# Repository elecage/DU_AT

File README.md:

# 열린플랫폼을 활용한 지역기반 보조기기 R&SD
환영합니다. 이 페이지는 동서울대학교, 인하대학교, 성남시장애인종합복지관이 공동으로 운영하는 지역기반 보조기기 R&amp;SD 과제의 보조기기 관리를 위해 만들어졌습니다.

## 과제 개요
  * 주관연구기관 : 동서울대학교산학협력단
  * 공동연구기관 : 인하대학교산학협력단/성남시장애인종합복지관
  * 연구기간 : 2024.04.01 - 2027.12.31
  * 주관 부처 : 보건복지부 국립재활원

## 과제 목표

## 보조기기 개발 프로세스

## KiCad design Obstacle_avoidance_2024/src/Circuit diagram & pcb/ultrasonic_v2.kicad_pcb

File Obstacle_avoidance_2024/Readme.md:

# 장애물 탐지 바닥센서

* 본 보조기기는 휠체어에 부착하여 후방의 장애물을 탐지하는 보조기기이다.
* 전동휠체어와 일반 휠체어에 부착하여 후진시 역과사고를 방지하는 것을 목적으로 한다.

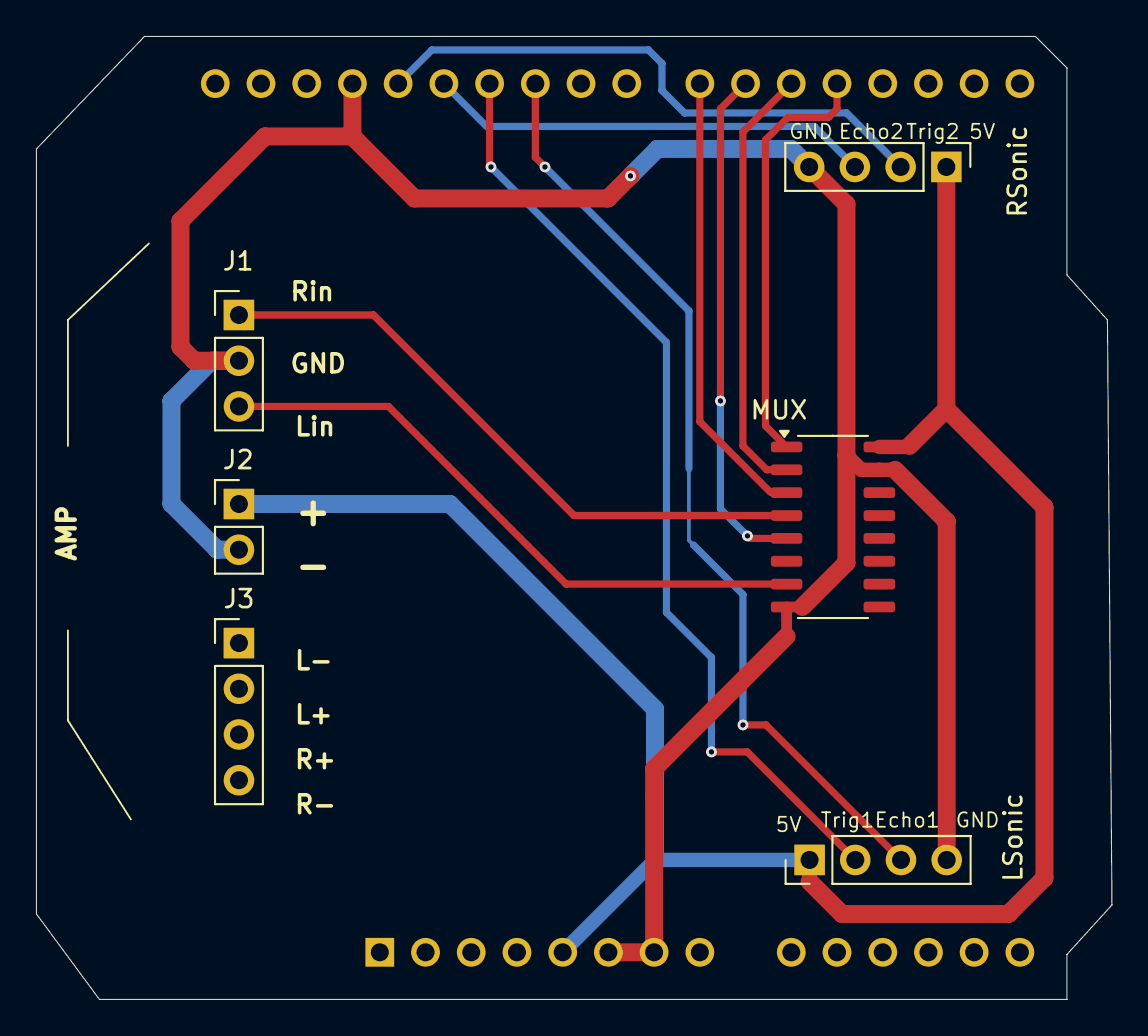
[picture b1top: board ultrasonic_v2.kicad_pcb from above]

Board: 2 copper layers, 59.8 x 53.5 mm, 7 parts (1 on the bottom side), 12 nets.

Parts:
A1: Arduino_UNO_R3
J1: Conn_01x03; PinHeader_1x03_P2.54mm_Vertical
J2: Conn_01x02; PinHeader_1x02_P2.54mm_Vertical
J3: Conn_01x04; PinHeader_1x04_P2.54mm_Vertical
LSonic: Conn_01x04; PinHeader_1x04_P2.54mm_Vertical
MUX: 74LS157; SO-16_3.9x9.9mm_P1.27mm
RSonic: Conn_01x04; PinHeader_1x04_P2.54mm_Vertical

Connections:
+5V: A1.5 (+5V), J2.1, LSonic.1, MUX.16 (VCC), RSonic.1
/Echo1_pin: A1.25 (D10), RSonic.3
/Echo2_pin: A1.27 (D12), LSonic.3
/SND_IN_L: J1.3, MUX.7 (Zb)
/SND_IN_R: J1.1, MUX.4 (Za)
/Trig1_pin: A1.26 (D11), RSonic.2
/Trig2_pin: A1.28 (D13), LSonic.2
GND: A1.6 (GND), A1.7 (GND), A1.29 (GND), J1.2, J2.2, LSonic.4, MUX.8 (GND), MUX.15 (E), RSonic.4
unnamed: A1.19 (D4), MUX.1 (S)
unnamed: A1.20 (D5), MUX.2 (I0a)
unnamed: A1.21 (D6), MUX.5 (I0b)
unnamed: A1.22 (D7), MUX.3 (I1a), MUX.6 (I1b)

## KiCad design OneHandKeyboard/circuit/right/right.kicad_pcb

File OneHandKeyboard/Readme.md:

# 한손키보드
## 

## Bill of Materials

| 품목 | 품명 | 규격 | 수량 | 구매처 |
|---|---|---|---|---|
|아크릴판| . | 1.5T | 1 | 문구점 |
|터치패드 모듈 |  TM035035-2024-001 | 커패시턴스 터치 센서 모듈 35mm Round SPI/I2C adhesive overlay | 1 | https://www.devicemart.co.kr/goods/view?no=15469948 |
| 볼트 | . | M2x4mm | 10 | . |
| 스탠드오프 | . | M2x8mm x 5mm(두께) | 5 | http://e.tb.cn/h.TWjAYGBWXisILQ2?tk=BHXE3v5Qo8o |
| PCB | 자체제작 | 왼손/오른손| 1| . |
|하우징 | 자체제작 | PLA | 1 | . |
|와이어 | . |. |. |.|
|마그네틱 포고핀| . | 수컷 암컷 간격, 2.5mm 용수철 부하| 1set|https://a.aliexpress.com/_oBtp4LP|
| 저소음스위치|.|Cherry MX 호환, 저소음 | 29 | .|
|키캡 | . |Cherry MX 호환, 무각 |. |.|
|펌웨어 | 자체제작 | . | . | .|

## 키보드 연습 사이트
https://cosmosalad.github.io/onekeytype/

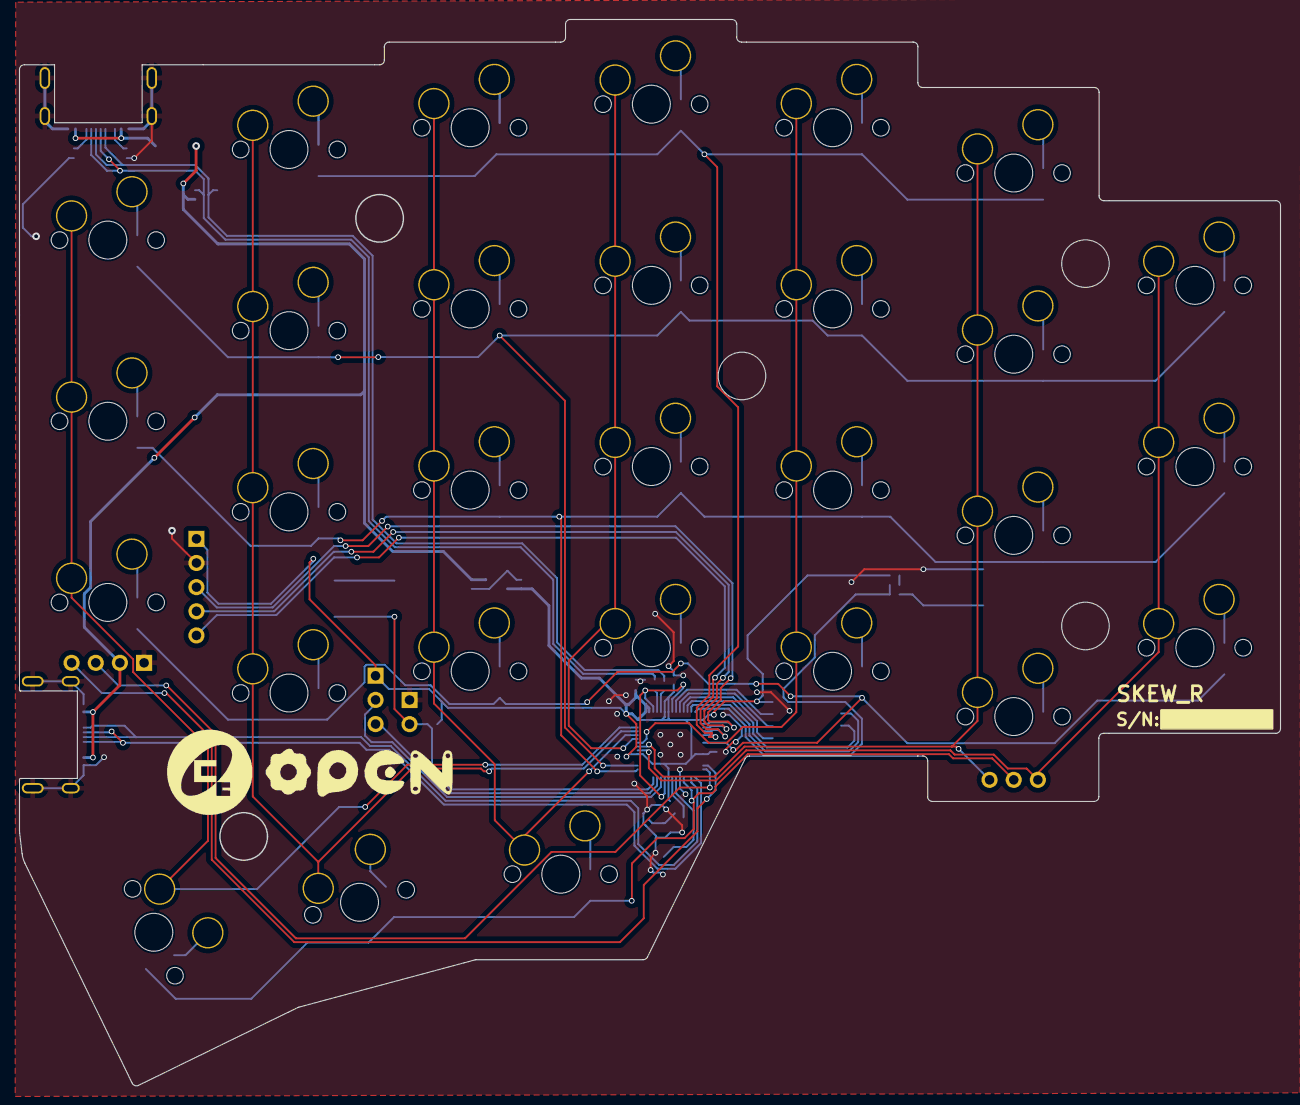
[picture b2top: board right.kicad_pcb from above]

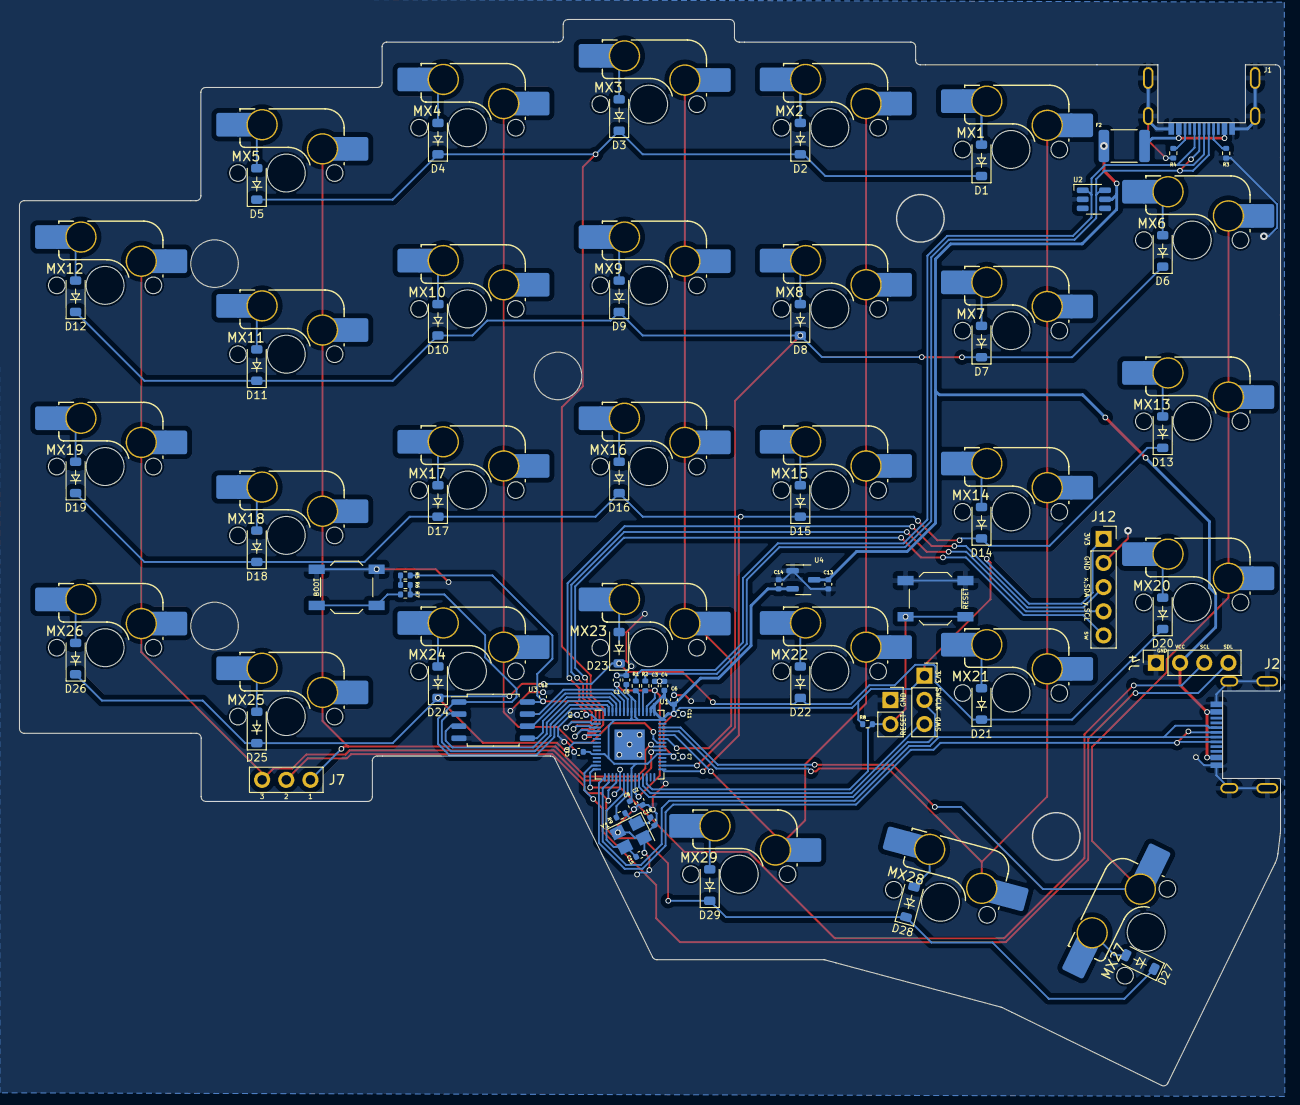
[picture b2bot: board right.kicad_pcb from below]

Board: 2 copper layers, 132.5 x 112.1 mm, 98 parts (96 on the bottom side), 73 nets.

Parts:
BOOT2: SW_Push; SW_SPST_TL3342
C1, C2, C4, C5, C6, C7, C8, C9, C10: 100n; C_0402_1005Metric
C3, C11, C12, C13, C14: 1u; C_0402_1005Metric
C15, C16: 22p; C_0402_1005Metric
D1, D2, D3, D4, D5, D6, D7, D8, D9, D10, D11, D12, D13, D14, D15, D16, D17, D18, D19, D20, D21, D22, D23, D24, D25, D26, D27, D28, D29: D_Small; D_SOD-123_new
F2: MF-MSMF050-2; Fuse_1812_4532Metric
J1, J2: TYPE-C-31-M-13; HRO-TYPE-C-31-M-13
J3: SWD_PinSocket; PinSocket_1x03_P2.54mm_Vertical
J4: PinSocket_4P; PinHeader_1x04_P2.54mm_Vertical
J6: PinSocket_5P; PinHeader_1x05_P2.54mm_Vertical
J7: side_b_PinSocket; PinSocket_1x03_P2.54mm_Vertical
MX1, MX2, MX3, MX4, MX5, MX6, MX7, MX8, MX9, MX10, MX11, MX12, MX13, MX14, MX15, MX16, MX17, MX18, MX19, MX20, MX21, MX22, MX23, MX24, MX25, MX26, MX28, MX29: kailh hotswap socket; SW_MX_HS_1u
MX27: kailh hotswap socket; SW_MX_HS_1.5u
R1, R2: 27; R_0402_1005Metric
R3, R4, R5, R6, R8: 5.1k; R_0402_1005Metric
R7, R9: 1k; R_0402_1005Metric
RESET1: SW_Push; SW_SPST_TL3342
RESET2: PinSocket_2P; PinSocket_1x02_P2.54mm_Vertical
U1: RP2040; QFN-56-1EP_7x7mm_P0.4mm_EP3.2x3.2mm
U2: SRV05-4; SOT-23-6-routable
U3: W25Q128JVSIQ; SOIC-8_5.23x5.23mm_P1.27mm
U4: XC6206P332MR; SOT-23-3
Y1: X322512MSB4SI; Crystal_SMD_3225-4Pin_3.2x2.5mm

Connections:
+1V1R: C1.1, C2.1, C3.1, U1.23 (DVDD), U1.45 (VREG_VOUT), U1.50 (DVDD)
+3V3R: C4.1, C5.1, C6.1, C7.1, C8.1, C9.1, C10.1, C11.1, C12.1, C14.1, J3.1, J6.1, R5.2, R8.2, U1.1 (IOVDD), U1.10 (IOVDD), U1.22 (IOVDD), U1.33 (IOVDD), U1.42 (IOVDD), U1.43 (ADC_AVDD), U1.44 (VREG_IN), U1.48 (USB_VDD), U1.49 (IOVDD), U3.8 (VCC), U4.2 (VO)
+5VR: C13.1, F2.1, J2.A4 (VBUS), J2.A9 (VBUS), J2.B4 (VBUS), J2.B9 (VBUS), J4.2, U2.5 (VP), U4.3 (VI)
COL0_R: J7.3, MX12.1, MX19.1, MX26.1, U1.34 (GPIO22)
COL1_R: J7.1, MX5.1, MX11.1, MX18.1, MX25.1, U1.35 (GPIO23)
COL2_R: MX4.1, MX10.1, MX17.1, MX24.1, U1.36 (GPIO24)
COL3_R: MX3.1, MX9.1, MX16.1, MX23.1, U1.37 (GPIO25)
COL4_R: MX2.1, MX8.1, MX15.1, MX22.1, MX29.1, U1.38 (GPIO26_ADC0)
COL5_R: MX1.1, MX7.1, MX14.1, MX21.1, MX28.1, U1.39 (GPIO27_ADC1)
COL6_R: MX6.1, MX13.1, MX20.1, MX27.1, U1.40 (GPIO28_ADC2)
GNDR: BOOT2.1, C1.2, C2.2, C3.2, C4.2, C5.2, C6.2, C7.2, C8.2, C9.2, C10.2, C11.2, C12.2, C13.2, C14.2, C15.2, C16.1, J1.A1 (GND), J1.A12 (GND), J1.B1 (GND), J1.B12 (GND), J1.S1 (SHIELD), J2.A1 (GND), J2.A12 (GND), J2.B1 (GND), J2.B12 (GND), J2.S1 (SHIELD), J4.1, J6.2, R3.2, R4.2, RESET1.1, RESET2.1, U1.19 (TESTEN), U1.57 (GND), U2.2 (VN), U3.4 (GND), U4.1 (GND), Y1.2, Y1.4
unnamed: BOOT2.2, R7.1
unnamed: C16.2, R9.1, Y1.1
unnamed: D1.2 (A), MX1.2
unnamed: D2.2 (A), MX2.2
unnamed: D3.2 (A), MX3.2
unnamed: D4.2 (A), MX4.2
unnamed: D5.2 (A), MX5.2
unnamed: D6.2 (A), MX6.2
unnamed: D7.2 (A), MX7.2
unnamed: D8.2 (A), MX8.2
unnamed: D9.2 (A), MX9.2
unnamed: D10.2 (A), MX10.2
unnamed: D11.2 (A), MX11.2
unnamed: D12.2 (A), MX12.2
unnamed: D13.2 (A), MX13.2
unnamed: D14.2 (A), MX14.2
unnamed: D15.2 (A), MX15.2
unnamed: D16.2 (A), MX16.2
unnamed: D17.2 (A), MX17.2
unnamed: D18.2 (A), MX18.2
unnamed: D19.2 (A), MX19.2
unnamed: D20.2 (A), MX20.2
unnamed: D21.2 (A), MX21.2
unnamed: D22.2 (A), MX22.2
unnamed: D23.2 (A), MX23.2
unnamed: D24.2 (A), MX24.2
unnamed: D25.2 (A), MX25.2
unnamed: D26.2 (A), MX26.2
unnamed: D27.2 (A), MX27.2
unnamed: D28.2 (A), MX28.2
unnamed: D29.2 (A), MX29.2
unnamed: J1.A5 (CC1), R3.1
unnamed: J1.B5 (CC2), R4.1
unnamed: R5.1, R6.2
unnamed: R2.2, U1.46 (USB_DM)
unnamed: R1.2, U1.47 (USB_DP)
QSPI_SCLK_R: U1.52 (QSPI_SCLK), U3.6 (CLK)
QSPI_SD0_R: U1.53 (QSPI_SD0), U3.5 (DI(IO0))
QSPI_SD1_R: U1.55 (QSPI_SD1), U3.2 (DO(IO1))
QSPI_SD2_R: U1.54 (QSPI_SD2), U3.3 (IO2)
QSPI_SD3_R: U1.51 (QSPI_SD3), U3.7 (IO3)
QSPI_SS_R: R6.1, R7.2, U1.56 (QSPI_SS), U3.1 (~CS)
RESET_R: R8.1, RESET1.2, RESET2.2, U1.26 (RUN)
ROW0_R: D1.1 (K), D2.1 (K), D3.1 (K), D4.1 (K), D5.1 (K), U1.5 (GPIO3)
ROW1_R: D6.1 (K), D7.1 (K), D8.1 (K), D9.1 (K), D10.1 (K), D11.1 (K), D12.1 (K), U1.30 (GPIO19)
ROW2_R: D13.1 (K), D14.1 (K), D15.1 (K), D16.1 (K), D17.1 (K), D18.1 (K), D19.1 (K), U1.29 (GPIO18)
ROW3_R: D20.1 (K), D21.1 (K), D22.1 (K), D23.1 (K), D24.1 (K), D25.1 (K), D26.1 (K), U1.7 (GPIO5)
ROW4_R: D27.1 (K), D28.1 (K), D29.1 (K), J7.2, U1.18 (GPIO15)
SCL_R: J4.3, U1.14 (GPIO11)
SDA_R: J4.4, U1.13 (GPIO10)
SPI0_RX_R: J2.A6 (D+), J2.B6 (D+), U1.16 (GPIO13)
SPI0_TX_R: J2.A7 (D-), J2.B7 (D-), U1.15 (GPIO12)
SWCLK_R: J3.2, U1.24 (SWCLK)
SWD_R: J3.3, U1.25 (SWD)
USB_D+_R: J1.A6 (D+), J1.B6 (D+), R1.1, U2.1 (IO1)
USB_D-_R: J1.A7 (D-), J1.B7 (D-), R2.1, U2.6 (IO4)
VBUSR: F2.2, J1.A4 (VBUS), J1.A9 (VBUS), J1.B4 (VBUS), J1.B9 (VBUS)
XIN_R: C15.1, U1.20 (XIN), Y1.3
XOUT_R: R9.2, U1.21 (XOUT)
sw_R: J6.5, U1.4 (GPIO2)
vrx_R: J6.3, U1.2 (GPIO0)
vry_R: J6.4, U1.3 (GPIO1)

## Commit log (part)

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2024-04-11 다용도 오프너 추가
    다용도 오프너 추가
2024-04-11 사용스토리 업로드
2024-04-23 연구목표 업로드
2024-04-23 그림파일명 변경
2024-04-23 개발프로세스 그림 업로드
2024-07-03 Create README.md
    장애물 인식 바닥센서 폴더 생성
2024-07-03 장애물 센서 하부 디렉터리 생성
2024-07-03 Create test.py
    이것은 test 파일입니다.
2024-07-23 7월 23일자 AI based, Camera based코드 추가
2024-08-02 Update README.md
    요구사항 및 기능 추가
2024-11-18 Create Obstacle_Avoidance_SensorCircuit diagram & pcb
2024-11-18 Create Circuit diagram & pcb
2024-11-18 Create sample
2024-12-19 한손키보드 업로드
2024-12-21 Create STL 모델링 파일
2024-12-27 한손키보드 소스 업로드
2024-12-27 Create Real_Ultrasonic_Obstacle_detection
    12월27일자 코드 추가
2024-12-27 Rename Real_Ultrasonic_Obstacle_detection to Real_Ultrasonic_Obstacle_detection.ino
2025-02-04 Add files via upload
    2025_02_04 기존 장애물 탐지 알고리즘 함수화 작업-
2025-02-04 2025_02_04 기존 장애물 탐지 알고리즘 함수화 작업
    - 기존 코드에서 장애물 탐지 알고리즘을 함수 기반으로 리팩토링하여 코드의 가독성과 유지보수성을 향상
2025-02-04 2025_02_04 기존 장애물 탐지 알고리즘 함수화 작업
    - 2025_02_04 기존 코드에서 장애물 탐지 알고리즘을 함수 기반으로 리팩토링하여 코드의 가독성과 유지보수성을 향상
2025-05-14 청각장애인 안내시스템 및 시각장애인안내견 음성안내기 폴더 생성
2025-05-14 안내견 음성안내기 요구사항 분석 업로드
2025-05-14 Readme.md 추가
2025-05-19 사운드 인디케이터 소스코드 및 MP3 파일 업로드
2025-07-14 Create topic.md
    청각장애인 시스템용 토픽 메시지 정리 파일 생성
2025-07-22 40mm 터치모듈 3D 모델 및 펌웨어 업로드
2025-09-16 Create 한손 키보드 예전파일
2025-09-16 Rename OneHandKeyboard/case/SKEW_LEFT.stl to OneHandKeyboard/case/backup/SKEW_LEFT.stl
2025-10-27 코드 수정 및 MP3 파일 수정
2025-11-10 Create 2024
2025-11-10 Add files via upload
    2025 버전 업데이트
2025-11-10 Rename AI 화재감지 제작 매뉴얼.pdf to AI 화재감지 카메라 제작 매뉴얼.pdf
2025-11-11 Create MQTT_Server_Code
2025-11-11 Add MQTT decision server implementation
    Initial implementation of MQTT decision server with various functionalities including device control, logging, and status publishing.
2025-11-11 handlers.py
    Implement various handlers for sensor events including fire, gas, and water level detection. Each handler publishes appropriate alerts and manages device states.
2025-11-11 MQTT_config.json
    Added configuration for various sensors including shz, mq7, gas, AI fire alert, water level, and doorbell.
2025-11-11 handler_registry.py
2025-11-11 Add Firebase utility functions for FCM
    Implement Firebase utility functions for FCM token management and message sending.
2025-11-11 Add Firebase service account JSON configuration
2025-11-11 Add MQTT doorbell publisher functionality
    Implement doorbell MQTT publisher with button handling.
2025-11-11 Add MQTTClient implementation for MQTT protocol
2025-11-11 Add fire sensing MQTT publisher functionality
2025-11-11 Add gas sensor MQTT publisher functionality
    Implement gas sensor monitoring with MQTT publishing.
2025-11-11 Add MQTT subscriber for beacon functionality
    Implement MQTT subscriber for beacon control using MicroPython.
2025-11-11 Add MQTTClient class for MQTT communication
2025-11-11 Update print statement from 'Hello' to 'Goodbye'
2025-11-11 Create Appzipfile
2025-11-11 Add google-service.json for Firebase configuration
2025-11-11 Create 1
2025-11-11 Add gradle.properties for project configuration
2025-11-11 Add settings.gradle.kts for project configuration
    Initialize Gradle settings with repositories and project name.
2025-11-11 CarrierAssistant 추가
    물건들기보조기기
2025-11-11 Add README for 물건들기 보조기기 project
2025-11-17 Add files via upload
    2025 version
2025-11-18 Create Obstacle_Avoidance_Sensor
2025-11-18 Add files via upload
    Restore Obstacle_Avoidance_Sensor folder
2025-11-18 Rename requirements.txt to Obstacle_Avoidance_Sensor/requirements.txt
2025-11-18 Rename README.md to Obstacle_Avoidance_Sensor/README.md
2025-11-18 Create Ultrasonic
2025-11-18 Rename Obstacle_Avoidance_Sensor/디스플레이고정부1.stl to Obstacle_Avoidance_Sensor/3D Modeling/디스플레이고정부1.stl
2025-11-18 Rename Obstacle_Avoidance_Sensor/디스플레이고정부2.stl to Obstacle_Avoidance_Sensor/3D Modeling/디스플레이고정부2.stl
2025-11-18 Rename Obstacle_Avoidance_Sensor/디스플레이고정부3.stl to Obstacle_Avoidance_Sensor/3D Modeling /디스플레이고정부3.stl
2025-11-18 Rename Obstacle_Avoidance_Sensor/디스플레이고정부4.stl to Obstacle_Avoidance_Sensor/3D Modeling /디스플레이고정부4.stl
2025-11-18 Rename Obstacle_Avoidance_Sensor/디스플레이후면.stl to Obstacle_Avoidance_Sensor/3D Modeling /디스플레이후면.stl
2025-11-18 Rename Obstacle_Avoidance_Sensor/모듈1.stl to Obstacle_Avoidance_Sensor/3D Modeling /모듈1.stl
2025-11-18 Rename Obstacle_Avoidance_Sensor/모듈2.stl to Obstacle_Avoidance_Sensor/3D Modeling /모듈2.stl
2025-11-18 Rename Obstacle_Avoidance_Sensor/모듈3.stl to Obstacle_Avoidance_Sensor/3D Modeling /모듈3.stl
2025-11-18 Rename Obstacle_Avoidance_Sensor/모듈고정부1.stl to Obstacle_Avoidance_Sensor/3D Modeling /모듈고정부1.stl
2025-11-18 Rename Obstacle_Avoidance_Sensor/모듈고정부2.stl to Obstacle_Avoidance_Sensor/3D Modeling /모듈고정부2.stl
2025-11-18 Rename Obstacle_Avoidance_Sensor/모듈고정부3.stl to Obstacle_Avoidance_Sensor/3D Modeling /모듈고정부3.stl
2025-11-18 Rename Obstacle_Avoidance_Sensor/모듈고정부4.stl to Obstacle_Avoidance_Sensor/3D Modeling /모듈고정부4.stl
2025-11-18 Rename Obstacle_Avoidance_Sensor/카메라고정부1.stl to Obstacle_Avoidance_Sensor/3D Modeling /카메라고정부1.stl
2025-11-18 Rename Obstacle_Avoidance_Sensor/카메라고정부2.stl to Obstacle_Avoidance_Sensor/3D Modeling /카메라고정부2.stl
2025-11-18 Rename 디스플레이고정부1.stl to 디스플레이고정부1.stl
2025-11-18 Rename 디스플레이고정부2.stl to 디스플레이고정부2.stl
2025-11-18 Rename Obstacle_Avoidance_Sensor/Object_Detect_Camera.py to Obstacle_Avoidance_Sensor/AIBased/Object_Detect_Camera.py
2025-11-18 Add README for obstacle avoidance sensor project
2025-11-18 Rename Obstacle_Avoidance_Sensor/AIBased/crackn.pt to Obstacle_Avoidance_Sensor/AIBased/AI Models/crackn.pt
2025-11-18 Rename Obstacle_Avoidance_Sensor/AIBased/pothole.pt to Obstacle_Avoidance_Sensor/AIBased/AI Models/pothole.pt
2025-11-18 Rename Obstacle_Avoidance_Sensor/AIBased/streetn.pt to Obstacle_Avoidance_Sensor/AIBased/AI Models/streetn.pt
2025-11-18 Rename Obstacle_Avoidance_Sensor/AIBased/yolov8n.pt to Obstacle_Avoidance_Sensor/AIBased/AI Models/yolov8n.pt
2025-11-18 Create CameraBased
2025-11-18 Create 11
2025-12-09 zip 파일 제거
2026-01-21 2024년 자료 업로드
2026-01-21 Create README for obstacle detection device
    Added a README file explaining the obstacle detection device for wheelchairs.
2026-01-21 Create README for smart mood lamp project
    Add a README file explaining the smart mood lamp's purpose and functionality for the hearing impaired.
2026-01-21 24년도 자료 추가
2026-01-21 Add initial README for mouth trainer device
2026-05-12 Rename 조립 및 회로도.pdf to 조립 및 회로도 메뉴얼.pdf
